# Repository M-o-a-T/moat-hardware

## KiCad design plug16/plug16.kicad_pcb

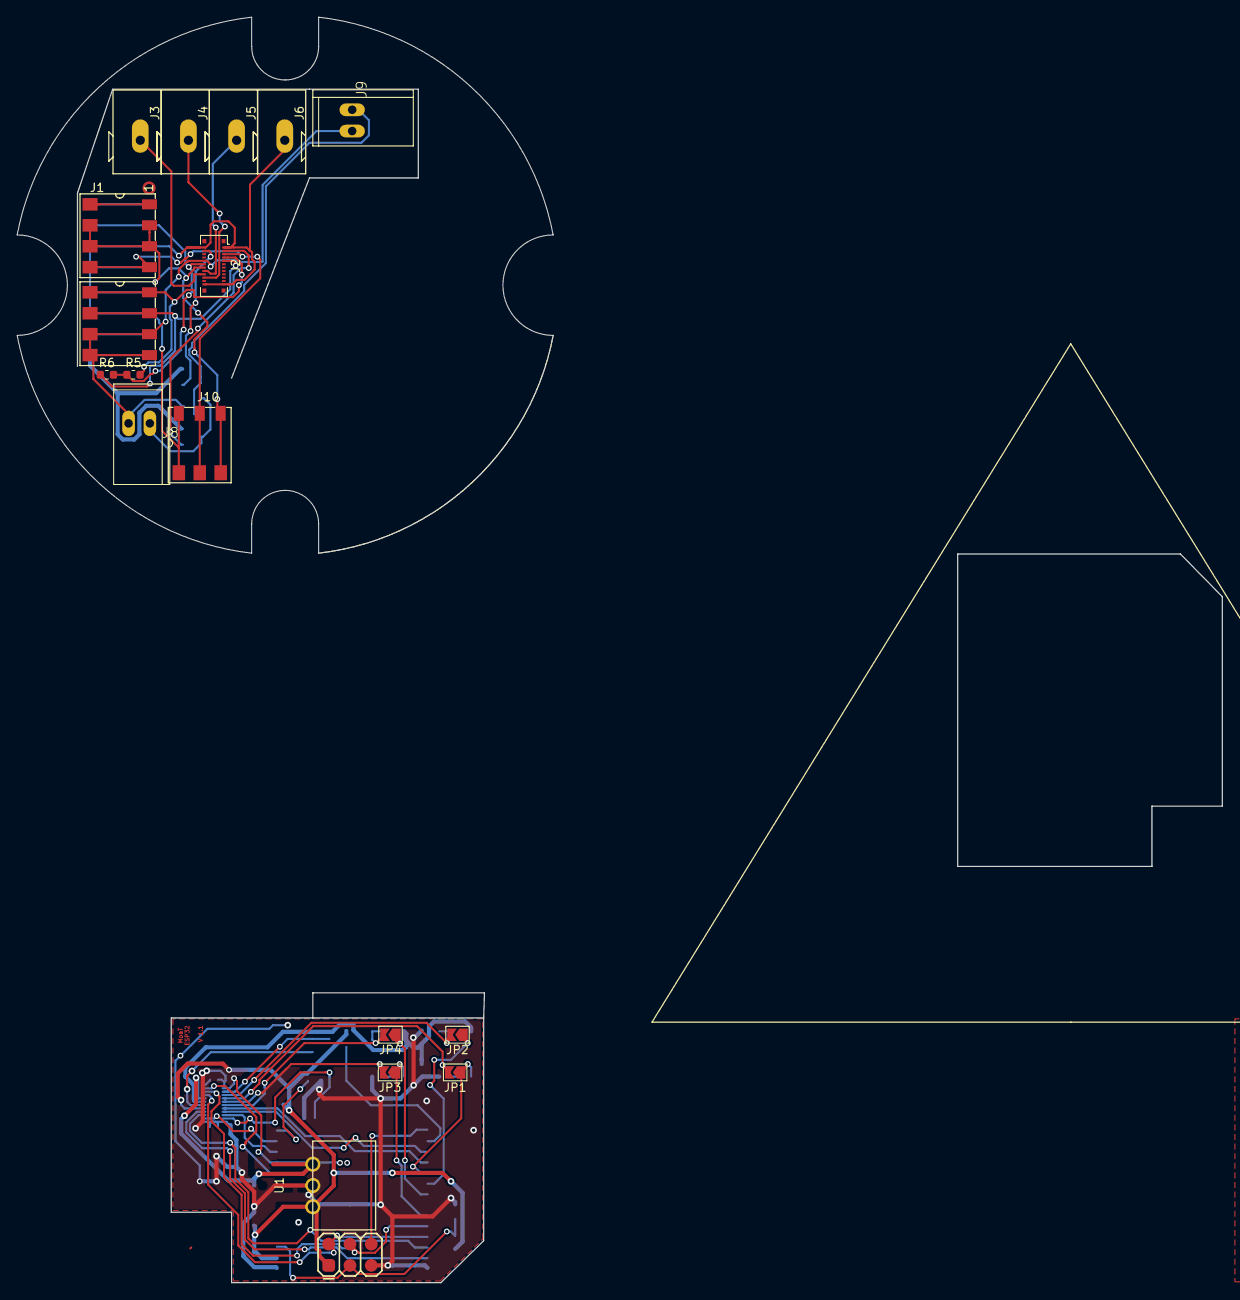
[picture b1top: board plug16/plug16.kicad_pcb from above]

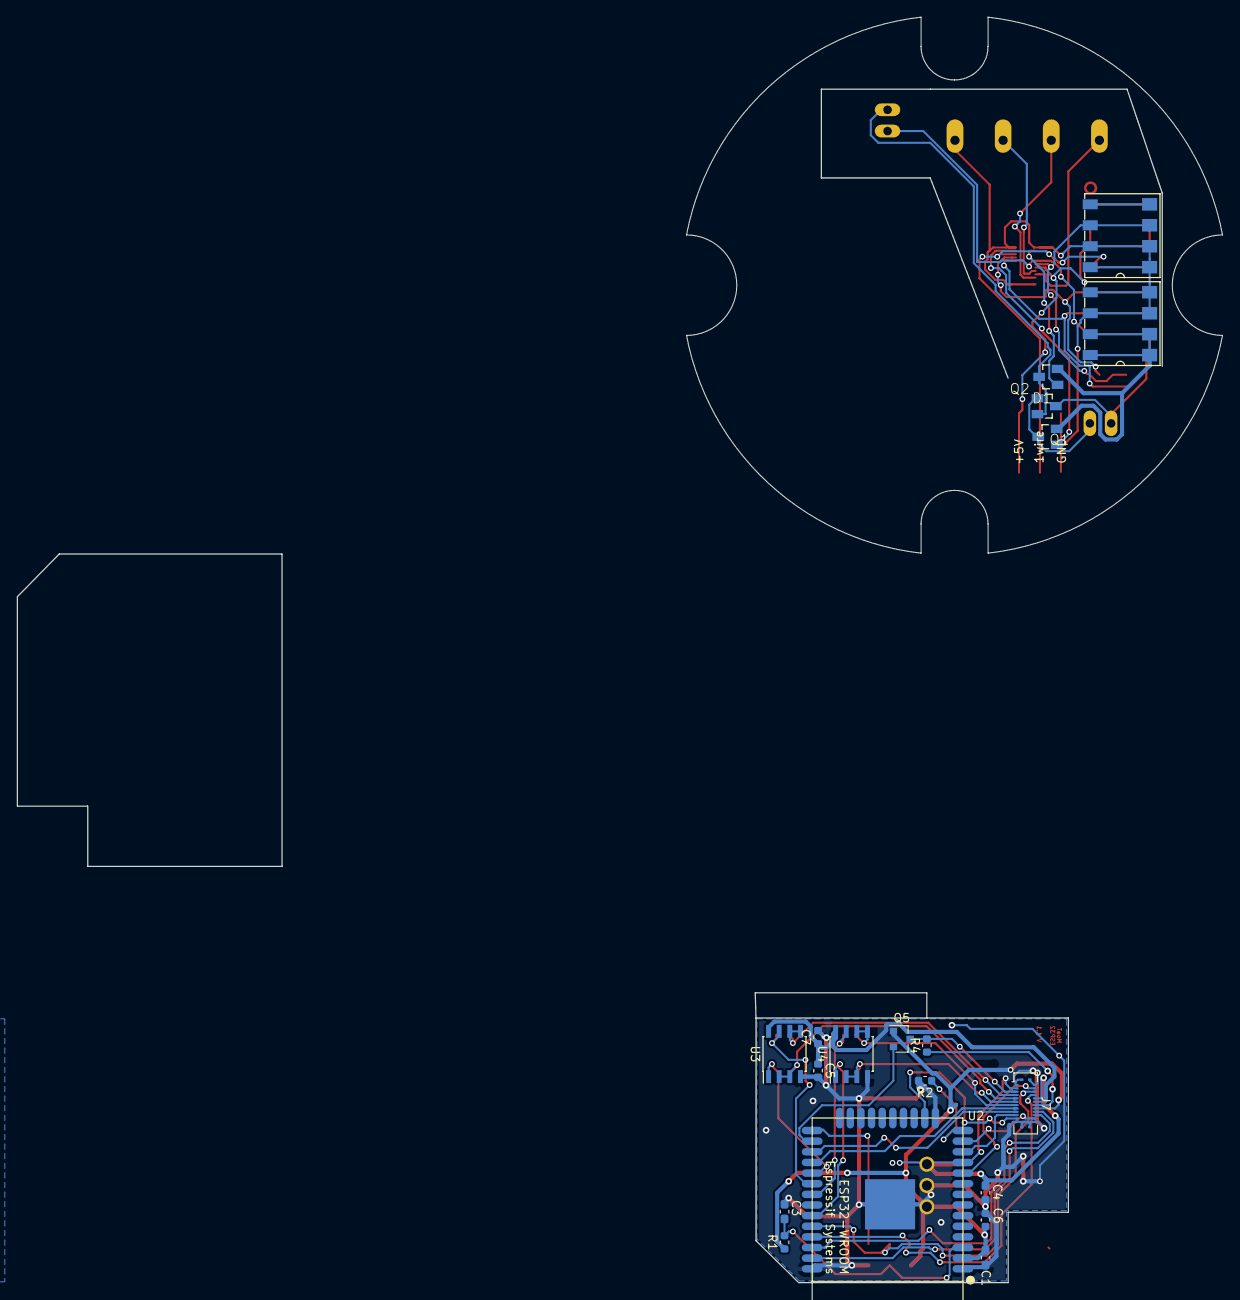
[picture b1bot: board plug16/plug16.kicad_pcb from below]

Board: 2 copper layers, 143.9 x 151.1 mm, 35 parts (17 on the bottom side), 44 nets.

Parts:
C1, C3: 100nF; C_0603_1608Metric_Pad1.05x0.95mm_HandSolder
C4: 10µF; C_0603_1608Metric_Pad1.05x0.95mm_HandSolder
C5, C7: 100n; C_0603_1608Metric
C6: 22µF; C_0603_1608Metric
D1: BAS40-05; SOT23
J1: Moat_Bus_16; Moat_16_2side
J2: Moat_Bus_wire; Molex_SlimStack_503772-24
J3: SCLK; Wago_Terminal_243
J4: SDA; Wago_Terminal_243
J5: 3V3; Wago_Terminal_243
J6: GND; Wago_Terminal_243
J7: Moat_Bus_device; Molex_SlimStack_503776-24
J8: S1; 1X02_GN
J9: S2; 1X02_GN
J10: 1wireConn; AVX_9276_3Pin
JP1, JP2, JP3, JP4: Jumper_NC; SolderJumper-2_P1.3mm_Open_TrianglePad1.0x1.5mm
Prog1: PogoPad; 2X3_PAD
Q1, Q2: 2N7002; SOT23
Q5: 2N7002; SOT-23
R1, R2, R4: 10k; R_0603_1608Metric
R5, R6: 470; R_0603_1608Metric
U1: VXO78; VXO078
U2: ESP-32S; ESP32-WROOM
U3, U4: P82B96; SOIC-8_3.9x4.9mm_P1.27mm
U$1: Val**; UNTERPUTZDOSE

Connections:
+3V3: C1.1, C6.1, J7.16, Prog1.1, Q5.1, R1.1, U1.3, U2.U1
+5V: J7.14, R4.1
+12V: C5.1, C7.1, J7.12, U3.8, U4.8
+24V: C4.1, J7.10, U1.1
/1wire: J7.5, Q5.3, R4.2
/BUS3: JP3.1, U2.42, U4.1
/BUS3_IN: J7.11, JP3.2, U4.2, U4.3
/BUS4: JP4.1, U2.38, U4.7
/BUS4_IN: J7.13, JP4.2, U4.5, U4.6
/EN: C3.1, Prog1.3, R1.2, U2.9
/RXD2: J7.17, U2.25
/Rx: J7.8, Prog1.2, U2.41
/S1: J2.3, Q1.1
/S2: J2.4, Q2.1
/SCL: JP2.1, U2.35, U3.7
/SCL_IN: J7.7, JP2.2, U3.5, U3.6
/SCLx: J7.18, U2.36
/SDA: JP1.1, U2.34, U3.1
/SDA_IN: J7.9, JP1.2, U3.2, U3.3
/SDAx: J7.20, U2.39
/SW1: J7.3, U2.15
/SW2: J7.4, U2.14
/T1: J7.21, U2.20
/T2: J7.22, U2.17
/T3: J7.19, U2.16
/TXD2: J7.15, U2.27
/Tx: J7.6, Prog1.4, U2.40
GND: C1.2, C3.2, C4.2, C5.2, C6.2, C7.2, J7.1, J7.2, J7.23, J7.24, J7.MP, Prog1.5, R2.2, U1.2, U2.G1, U2.G2, U2.G3, U2.G4, U3.4, U4.4
GNDPWR: J1.14, J1.16, Q1.2, Q2.2
unnamed: D1.1, J8.1, Q1.3
unnamed: D1.2, J9.1, Q2.3
unnamed: D1.3, J1.13, J1.15, J2.10, J8.2, J9.2
unnamed: J1.3, J1.5, J2.14, J10.3
unnamed: J1.4, J2.12, R5.1, R6.2
unnamed: J1.7, J2.5, J10.2
unnamed: J1.9, J2.7, R5.2
unnamed: J1.6, J1.8, J1.10, J1.12, J2.1, J2.2, J2.23, J2.24, J6.1, J10.1
unnamed: J1.11, J2.9, R6.1
unnamed: J2.16, J5.1
unnamed: J2.18, J3.1
unnamed: J2.20, J4.1
unnamed: Prog1.6, U2.23
unnamed: Q5.2, U2.24
unnamed: R2.1, U2.18

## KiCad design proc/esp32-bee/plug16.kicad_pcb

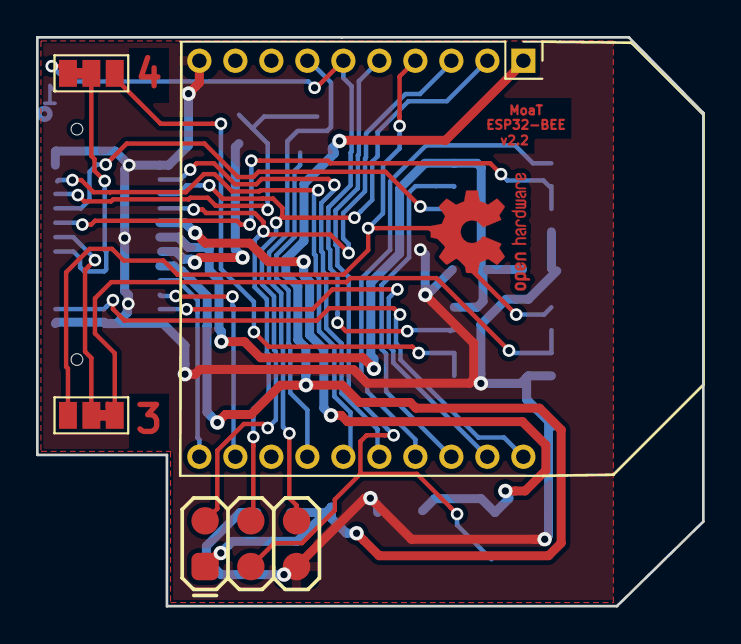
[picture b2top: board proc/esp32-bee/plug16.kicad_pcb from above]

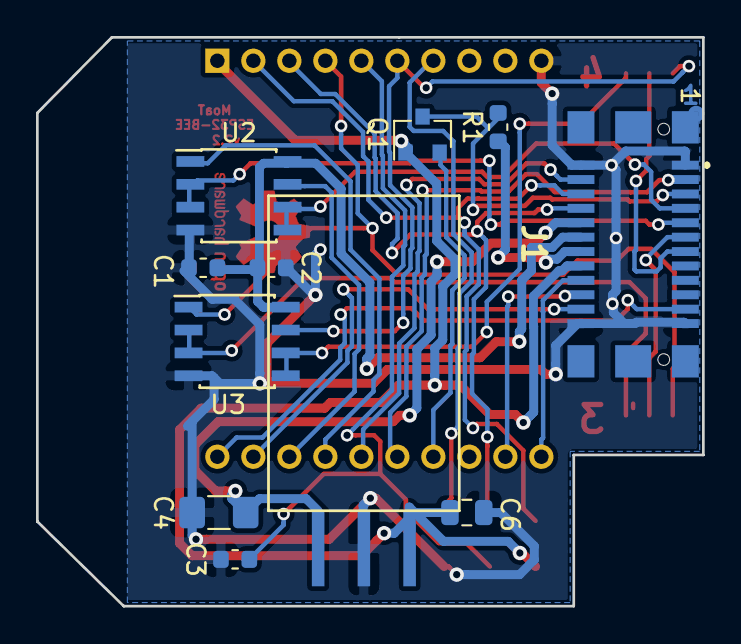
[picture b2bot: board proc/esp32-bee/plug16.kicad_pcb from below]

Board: 2 copper layers, 37.0 x 31.6 mm, 15 parts (11 on the bottom side), 27 nets.

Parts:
C1, C2: 100n; C_0603_1608Metric
C3: CP; C_0603_1608Metric
C4: 10µF; C_1206_3216Metric_Pad1.42x1.75mm_HandSolder
C6: 22µF; C_0805_2012Metric
J1: Moat_Bus_device; TE_1775013_plug
JP1, JP2: SolderJumper_3_Bridged12; SolderJumper-3_P1.3mm_Bridged12_Pad1.0x1.5mm_NumberLabels
Prog1: PogoPad; 2X3_PAD
Q1: 2N7002; SOT-23
R1: 10k; R_0603_1608Metric
U1: VXO78; VXO078_flat
U2, U3: P82B96; SOIC-8_3.9x4.9mm_P1.27mm
U5: ESPBEE

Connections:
+3V3: C6.1, J1.16, Prog1.1, Q1.1, U1.3, U5.1
+5V: J1.14, R1.1
+12V: C1.1, C2.1, J1.12, U2.8, U3.8
+24V: C4.1, J1.10, U1.1
/1w: Q1.2, U5.14
/Boot0: Prog1.6, U5.7
/Bus1: U2.7, U5.18
/Bus2: U2.1, U5.17
/Bus3: JP1.3, U3.1, U5.4
/Bus4: JP2.1, U3.7, U5.6
/Common bus interface/1wire_5: J1.5, Q1.3, R1.2
/Common bus interface/Bus1_12: J1.7, U2.5, U2.6
/Common bus interface/Bus2_12: J1.9, U2.2, U2.3
/Common bus interface/Bus3_12: J1.11, JP1.2
/Common bus interface/Bus4_12: J1.13, JP2.2
/EN: C3.1, Prog1.3, U5.5
/Rx: J1.8, Prog1.4, U5.3
/SCLx: J1.18, U5.11
/SDAx: J1.20, U5.12
/SW1: J1.3, U5.15
/SW2: J1.4, U5.16
/T1: J1.21, U5.20
/T2: J1.22, U5.19
/Tx: J1.6, Prog1.2, U5.2
GND: C1.2, C2.2, C3.2, C4.2, C6.2, J1.1, J1.2, J1.23, J1.24, Prog1.5, U1.2, U2.4, U3.4, U5.10
unnamed: JP1.1, U3.2, U3.3
unnamed: JP2.3, U3.5, U3.6

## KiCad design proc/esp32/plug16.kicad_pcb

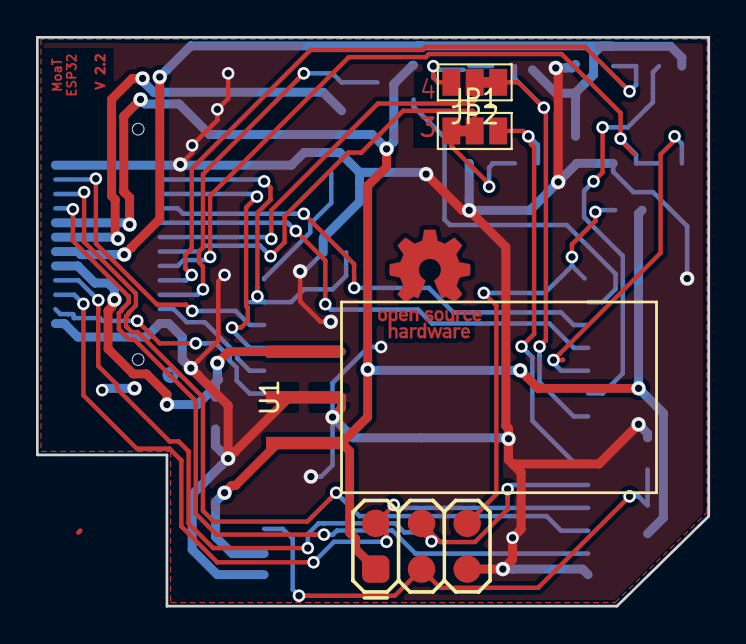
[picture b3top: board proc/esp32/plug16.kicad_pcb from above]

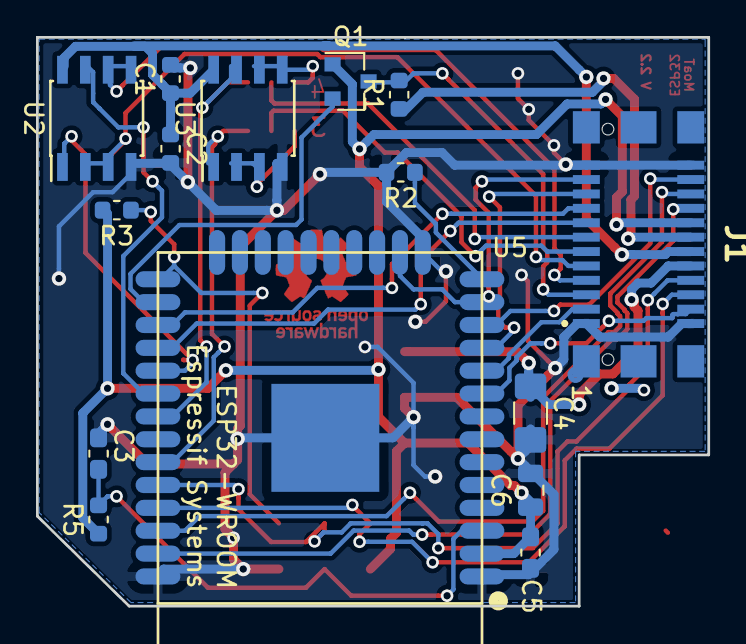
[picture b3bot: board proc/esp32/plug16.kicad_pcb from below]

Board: 2 copper layers, 37.3 x 31.6 mm, 19 parts (15 on the bottom side), 31 nets.

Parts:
C1, C2: 100n; C_0603_1608Metric
C3, C5: 100nF; C_0603_1608Metric_Pad1.05x0.95mm_HandSolder
C4: 10µF; C_1206_3216Metric_Pad1.42x1.75mm_HandSolder
C6: 22µF; C_0805_2012Metric
J1: Moat_Bus_device; TE_1775013_plug
JP1, JP2: SolderJumper_3_Bridged12; SolderJumper-3_P1.3mm_Bridged12_Pad1.0x1.5mm_NumberLabels
Prog1: PogoPad; 2X3_PAD
Q1: 2N7002; SOT-23
R1, R2, R3, R5: 10k; R_0603_1608Metric
U1: VXO78; VXO078_flat
U2, U3: P82B96; SOIC-8_3.9x4.9mm_P1.27mm
U5: ESP-32S; ESP32-WROOM

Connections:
+3V3: C5.1, C6.1, J1.16, Prog1.1, Q1.1, R3.2, R5.1, U1.3, U5.U1
+5V: J1.14, R1.1
+12V: C1.1, C2.1, J1.12, U2.8, U3.8
+24V: C4.1, J1.10, U1.1
/1wire: Q1.2, U5.24
/Boot0: Prog1.6, R3.1, U5.23
/Bus1: U2.7, U5.35
/Bus2: U2.1, U5.34
/Bus3: JP1.3, U3.1, U5.42
/Bus4: JP2.1, U3.7, U5.38
/Common bus interface/1wire_5: J1.5, Q1.3, R1.2
/Common bus interface/Bus1_12: J1.7, U2.5, U2.6
/Common bus interface/Bus2_12: J1.9, U2.2, U2.3
/Common bus interface/Bus3_12: J1.11, JP1.2
/Common bus interface/Bus4_12: J1.13, JP2.2
/EN: C3.1, Prog1.3, R5.2, U5.9
/Rx: J1.8, Prog1.4, U5.40
/Rx2: J1.17, U5.25
/SCLx: J1.18, U5.36
/SDAx: J1.20, U5.39
/SW1: J1.3, U5.14
/SW2: J1.4, U5.13
/T1: J1.21, U5.17, U5.20
/T2: J1.22, U5.16
/T3: J1.19, U5.15
/Tx: J1.6, Prog1.2, U5.41
/Tx2: J1.15, U5.27
GND: C1.2, C2.2, C3.2, C4.2, C5.2, C6.2, J1.1, J1.2, J1.23, J1.24, Prog1.5, R2.2, U1.2, U2.4, U3.4, U5.G1, U5.G2, U5.G3, U5.G4
unnamed: JP1.1, U3.2, U3.3
unnamed: JP2.3, U3.5, U3.6
unnamed: R2.1, U5.18

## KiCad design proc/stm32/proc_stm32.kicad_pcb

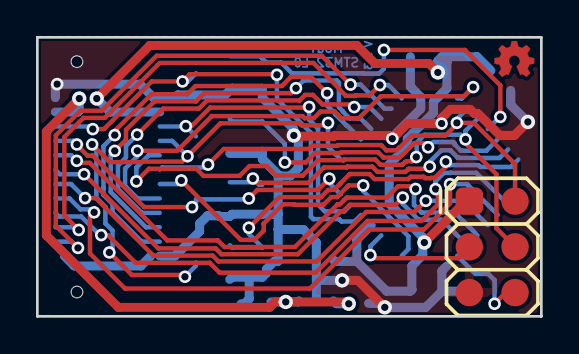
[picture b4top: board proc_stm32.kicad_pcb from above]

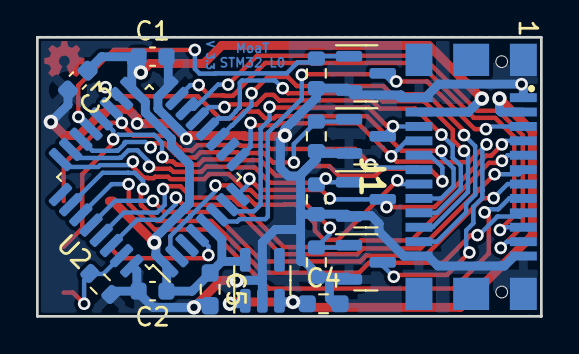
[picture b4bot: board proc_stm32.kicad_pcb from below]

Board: 2 copper layers, 28.0 x 15.5 mm, 18 parts (17 on the bottom side), 27 nets.

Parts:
C1, C2: 100nF; C_0603_1608Metric
C3: 10µF; C_0603_1608Metric
C4, C5: 1µF; R_0603_1608Metric_Pad0.98x0.95mm_HandSolder
J1: Moat_Compute_24; TE_1775013_plug
Prog1: PogoPad; 2X3_PAD
Q1, Q2, Q3, Q4: 2N7002; SOT-23
R1: 100k; R_0603_1608Metric
R2, R3, R4, R5: 1M; R_0603_1608Metric
U1: MIC5504; SOT-23-5
U2: STM32L051K8Tx; LQFP-32_7x7mm_P0.8mm

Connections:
+3V3: C1.1, C2.1, C3.1, C5.1, J1.4 (3V3), Prog1.1 (+3V), U1.5 (Vout), U2.1 (VDD), U2.5 (VDDA), U2.17 (VDD)
+5V: C4.1, J1.3 (5V), U1.1 (Vin), U1.3 (En)
/1wire: J1.14 (1W), U2.2 (PC14)
/Boot0: Prog1.6 (Boot0), R1.1, U2.31 (BOOT0)
/Bus1: J1.5 (Bus_1), Q1.3 (D), U2.6 (PA0)
/Bus1_out: Q1.1 (G), R2.1, U2.21 (PA11)
/Bus2: J1.6 (Bus_2), Q2.3 (D), U2.7 (PA1)
/Bus2_out: Q2.1 (G), R3.1, U2.22 (PA12)
/Bus3: J1.7 (Bus_3), Q3.3 (D), U2.8 (PA2)
/Bus3_out: Q3.1 (G), R4.1, U2.23 (PA13)
/Bus4: J1.8 (Bus_4), Q4.3 (D), U2.9 (PA3)
/Bus4_out: Q4.1 (G), R5.1, U2.24 (PA14)
/EN: Prog1.3 (Reset), U2.4 (NRST)
/Rx: J1.10 (Rx), Prog1.4 (Rx), U2.20 (PA10)
/SCLx: J1.9 (Clk), U2.29 (PB6)
/SDAx: J1.11 (Dat), U2.30 (PB7)
/SW1: J1.21 (S1), U2.14 (PB0)
/SW2: J1.19 (S2), U2.15 (PB1)
/SW3: J1.17 (S3), U2.26 (PB3)
/SW4: J1.15 (S4), U2.27 (PB4)
/T1: J1.22 (T1), U2.11 (PA5)
/T2: J1.20 (T2), U2.12 (PA6)
/T3: J1.18 (T3), U2.13 (PA7)
/T4: J1.16 (T4), U2.18 (PA8)
/Tx: J1.12 (Tx), Prog1.2 (Tx), U2.19 (PA9)
/ena: J1.13 (S5), U2.28 (PB5)
GND: C1.2, C2.2, C3.2, C4.2, C5.2, J1.1 (GND), J1.2 (GND), J1.23 (GND), J1.24 (GND), Prog1.5 (GND), Q1.2 (S), Q2.2 (S), Q3.2 (S), Q4.2 (S), R1.2, R2.2, R3.2, R4.2, R5.2, U1.2 (GND), U2.16 (VSS), U2.32 (VSS)

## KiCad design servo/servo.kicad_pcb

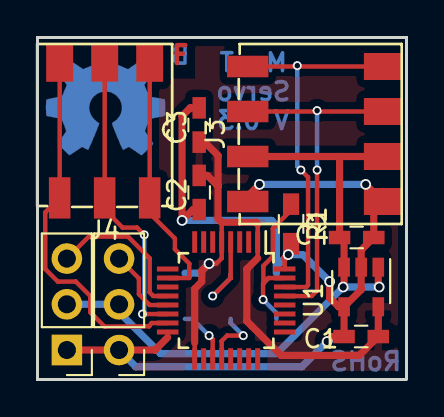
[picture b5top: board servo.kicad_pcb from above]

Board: 2 copper layers, 20.5 x 19.0 mm, 12 parts (1 on the bottom side), 14 nets.

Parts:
C1, C4: 1µF; C_0603_HandSoldering
C2: 10nF; C_0603_HandSoldering
C3: 100nF; C_0603_HandSoldering
J1: Servo 1; Pin_Header_Straight_1x03_Pitch2.54mm
J2: Servo 2; Pin_Header_Straight_1x03_Pitch2.54mm
J3: System; AVX_9276_4Pin_HS
J4: I/O; AVX_9276_3Pin_HS
Prog1: PogoPad; PogoPad_2x3_SMD
R1: 10k; R_0603_HandSoldering
U1: STM32F030K6Tx; LQFP-32_5x5mm_Pitch0.5mm
U2: TPS76333; SOT-23-5

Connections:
+3V3: C1.1, C2.1, C3.1, Prog1.1, U1.1, U1.5, U1.17, U2.5
+5V: C4.1, J1.2, J2.2, J3.2, U2.1, U2.3
/Rx: Prog1.4, U1.20
/SCL: J3.3, U1.29
/SDA: J3.4, U1.30
/Servo1: J1.3, U1.12
/Servo2: J2.3, U1.13
/Tx: Prog1.2, U1.19
GND: C1.2, C2.2, C3.2, C4.2, J1.1, J2.1, J3.1, Prog1.5, R1.2, U1.16, U1.32, U2.2, U2.4
unnamed: J4.1, U1.10
unnamed: J4.2, U1.14
unnamed: J4.3, U1.15
unnamed: Prog1.3, U1.4
unnamed: Prog1.6, R1.1, U1.31

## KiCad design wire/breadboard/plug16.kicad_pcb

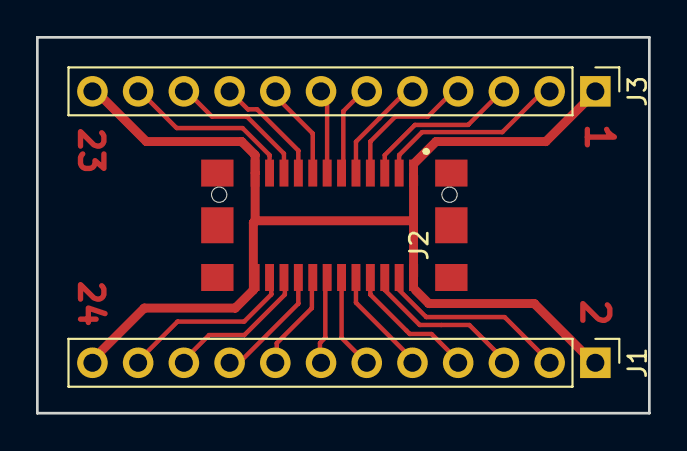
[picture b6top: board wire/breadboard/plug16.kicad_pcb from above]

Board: 2 copper layers, 34.0 x 20.9 mm, 3 parts (0 on the bottom side), 21 nets.

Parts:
J1, J3: Conn_01x12; PinHeader_1x12_P2.54mm_Vertical
J2: Moat_Bus_wire; TE-1775014-2

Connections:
GND: J1.1, J1.12, J2.1, J2.2, J2.23, J2.24, J3.1, J3.12
unnamed: J1.2, J2.4
unnamed: J1.3, J2.6
unnamed: J1.4, J2.8
unnamed: J1.5, J2.10
unnamed: J1.6, J2.12
unnamed: J1.7, J2.14
unnamed: J1.8, J2.16
unnamed: J1.9, J2.18
unnamed: J1.10, J2.20
unnamed: J1.11, J2.22
unnamed: J2.3, J3.2
unnamed: J2.5, J3.3
unnamed: J2.7, J3.4
unnamed: J2.9, J3.5
unnamed: J2.11, J3.6
unnamed: J2.13, J3.7
unnamed: J2.15, J3.8
unnamed: J2.17, J3.9
unnamed: J2.19, J3.10
unnamed: J2.21, J3.11
